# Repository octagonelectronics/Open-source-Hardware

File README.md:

# Open-source-Hardware
This repository contains all the Open-source hardware that we design.

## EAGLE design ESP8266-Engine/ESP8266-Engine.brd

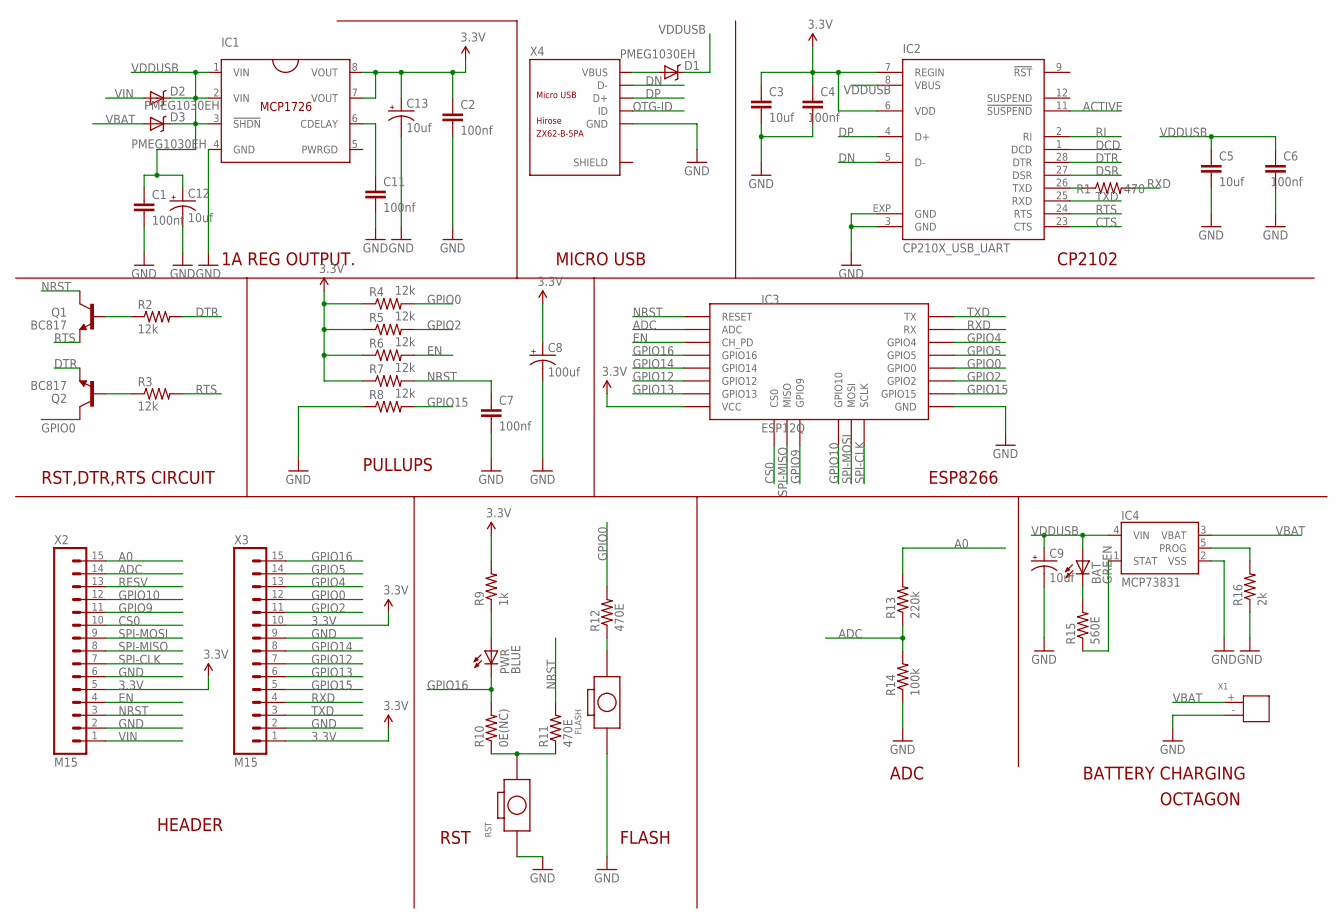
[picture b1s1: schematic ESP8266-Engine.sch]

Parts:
BAT: GREEN; LED-0603
C1, C2, C4, C6, C7, C11: 100nf; C0402
C3, C5: 10uf; C0603
C8: 100uf; EIA3216
C9, C12, C13: 10uf; EIA3216
D1, D2, D3: PMEG1030EH; MINIMELF
FLASH: SMD-BUTTON-WITHOUT-BOSS-(2P-3X2.5MM); SW2-SMD-3.0X2.5X1.2+0.4MM
IC1: MCP1726; SOIC8
IC2: CP210X_USB_UART; MLP28
IC3: ESP12Q
IC4: MCP73831; SOT23-5
PWR: BLUE; LED-0603
Q1, Q2: BC817; SOT23
R1: 470; R0402
R2, R3, R4, R5, R6, R7, R8: 12k; R0402
R9: 1k; R0402
R10: 0E(NC); R0402
R11, R12: 470E; R0402
R13: 220k; R0402
R14: 100k; R0402
R15: 560E; R0402
R16: 2k; R0402
RST: SMD-BUTTON-WITHOUT-BOSS-(2P-3X2.5MM); SW2-SMD-3.0X2.5X1.2+0.4MM
X1: DIP-JST-2P-2.0; H2-2.0-6X4.5MM
X2, X3: M15; 1X15
X4: MICRO-USB-SMD(ZX62-B-5PA); MICRO-USB5+6P-SMD-0.65-AB

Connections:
3.3V: C2.1, C3.1, C4.1, C8.A (+), C13.A (+), IC1.7 (VOUT), IC1.8 (VOUT), IC2.6 (VDD), IC2.7 (REGIN), IC3.VCC, R4.1, R5.1, R6.1, R7.1, R9.2, X2.5, X3.1, X3.10
A0: R13.2, X2.15
ACTIVE: IC2.11 (!SUSPEND)
ADC: IC3.ADC, R13.1, R14.2, X2.14
CS0: IC3.CS0, X2.10
CTS: IC2.23 (CTS)
DCD: IC2.1 (DCD)
DN: IC2.5 (D-), X4.2 (D-)
DP: IC2.4 (D+), X4.3 (D+)
DSR: IC2.27 (DSR)
DTR: IC2.28 (DTR), Q2.2 (E), R2.2
EN: IC3.EN (CH_PD), R6.2, X2.4
GND: C1.2, C2.2, C3.2, C4.2, C5.2, C6.2, C7.2, C8.C (-), C9.C (-), C11.2, C12.C (-), C13.C (-), FLASH.1, IC1.4 (GND), IC2.3 (GND), IC2.EXP (GND), IC3.GND, IC4.2 (VSS), R8.1, R14.1, R16.1, RST.1, X1.-, X2.2, X2.6, X3.2, X3.9, X4.5 (GND)
GPIO0: IC3.GPIO0, Q2.3 (C), R4.2, R12.2, X3.12
GPIO2: IC3.GPIO2, R5.2, X3.11
GPIO4: IC3.GPIO4, X3.13
GPIO5: IC3.GPIO5, X3.14
GPIO9: IC3.GPIO9, X2.11
GPIO10: IC3.GPIO10, X2.12
GPIO12: IC3.GPIO12, X3.7
GPIO13: IC3.GPIO13, X3.6
GPIO14: IC3.GPIO14, X3.8
GPIO15: IC3.GPIO15, R8.2, X3.5
GPIO16: IC3.GPIO16, PWR.C, R10.2, X3.15
unnamed: Q1.1 (B), R2.1
unnamed: IC2.26 (TXD), R1.1
unnamed: Q2.1 (B), R3.1
unnamed: BAT.C, R15.2
unnamed: IC4.1 (STAT), R15.1
unnamed: FLASH.2, R12.1
unnamed: PWR.A, R9.1
unnamed: R10.1, R11.1, RST.2
unnamed: IC4.5 (PROG), R16.2
unnamed: C11.1, IC1.6 (CDELAY)
NRST: C7.1, IC3.RESET, Q1.3 (C), R7.2, R11.2, X2.3
OTG-ID: X4.4 (ID)
RESV: X2.13
RI: IC2.2 (RI)
RTS: IC2.24 (RTS), Q1.2 (E), R3.2
RXD: IC3.RX, R1.2, X3.4
SPI-CLK: IC3.SCLK, X2.7
SPI-MISO: IC3.MISO, X2.8
SPI-MOSI: IC3.MOSI, X2.9
TXD: IC2.25 (RXD), IC3.TX, X3.3
VBAT: D3.A, IC4.3 (VBAT), X1.+
VBUS: D1.A, X4.1 (VBUS)
VDDUSB: BAT.A, C1.1, C5.1, C6.1, C9.A (+), C12.A (+), D1.K (C), D2.K (C), D3.K (C), IC1.1 (VIN), IC1.2 (VIN), IC1.3 (!SHDN), IC2.8 (VBUS), IC4.4 (VIN)
VIN: D2.A, X2.1

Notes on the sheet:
OCTAGON
1A REG OUTPUT.
MICRO USB
CP2102
RST,DTR,RTS CIRCUIT
PULLUPS
ESP8266
HEADER
RST
FLASH
ADC
BATTERY CHARGING

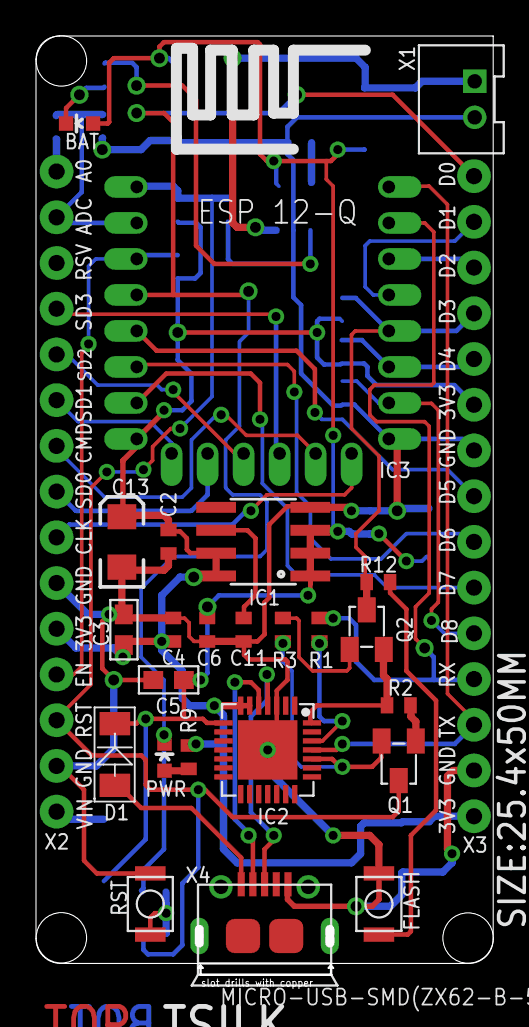
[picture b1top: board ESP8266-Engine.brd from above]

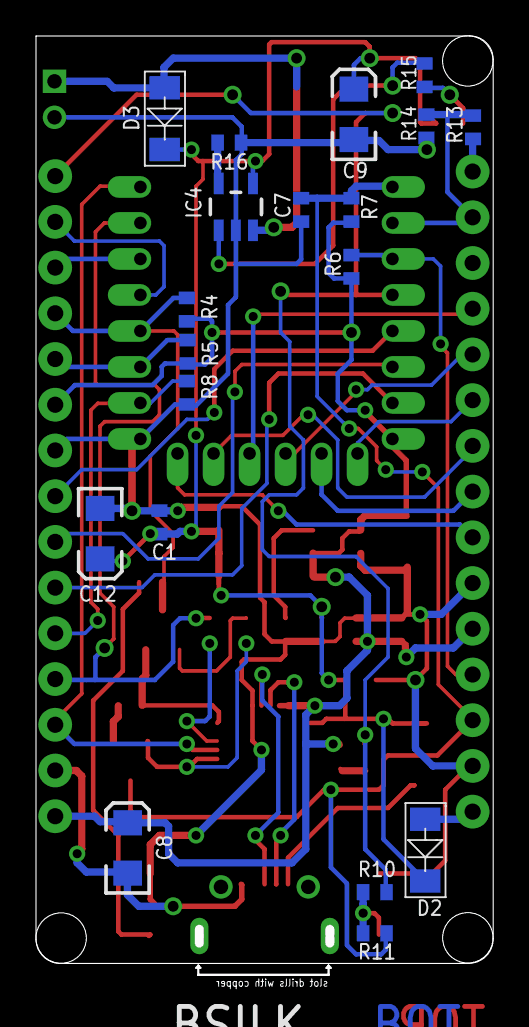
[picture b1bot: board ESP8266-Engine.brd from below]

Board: 2 copper layers, 24.9 x 52.5 mm, 45 parts (19 on the bottom side), 41 nets.

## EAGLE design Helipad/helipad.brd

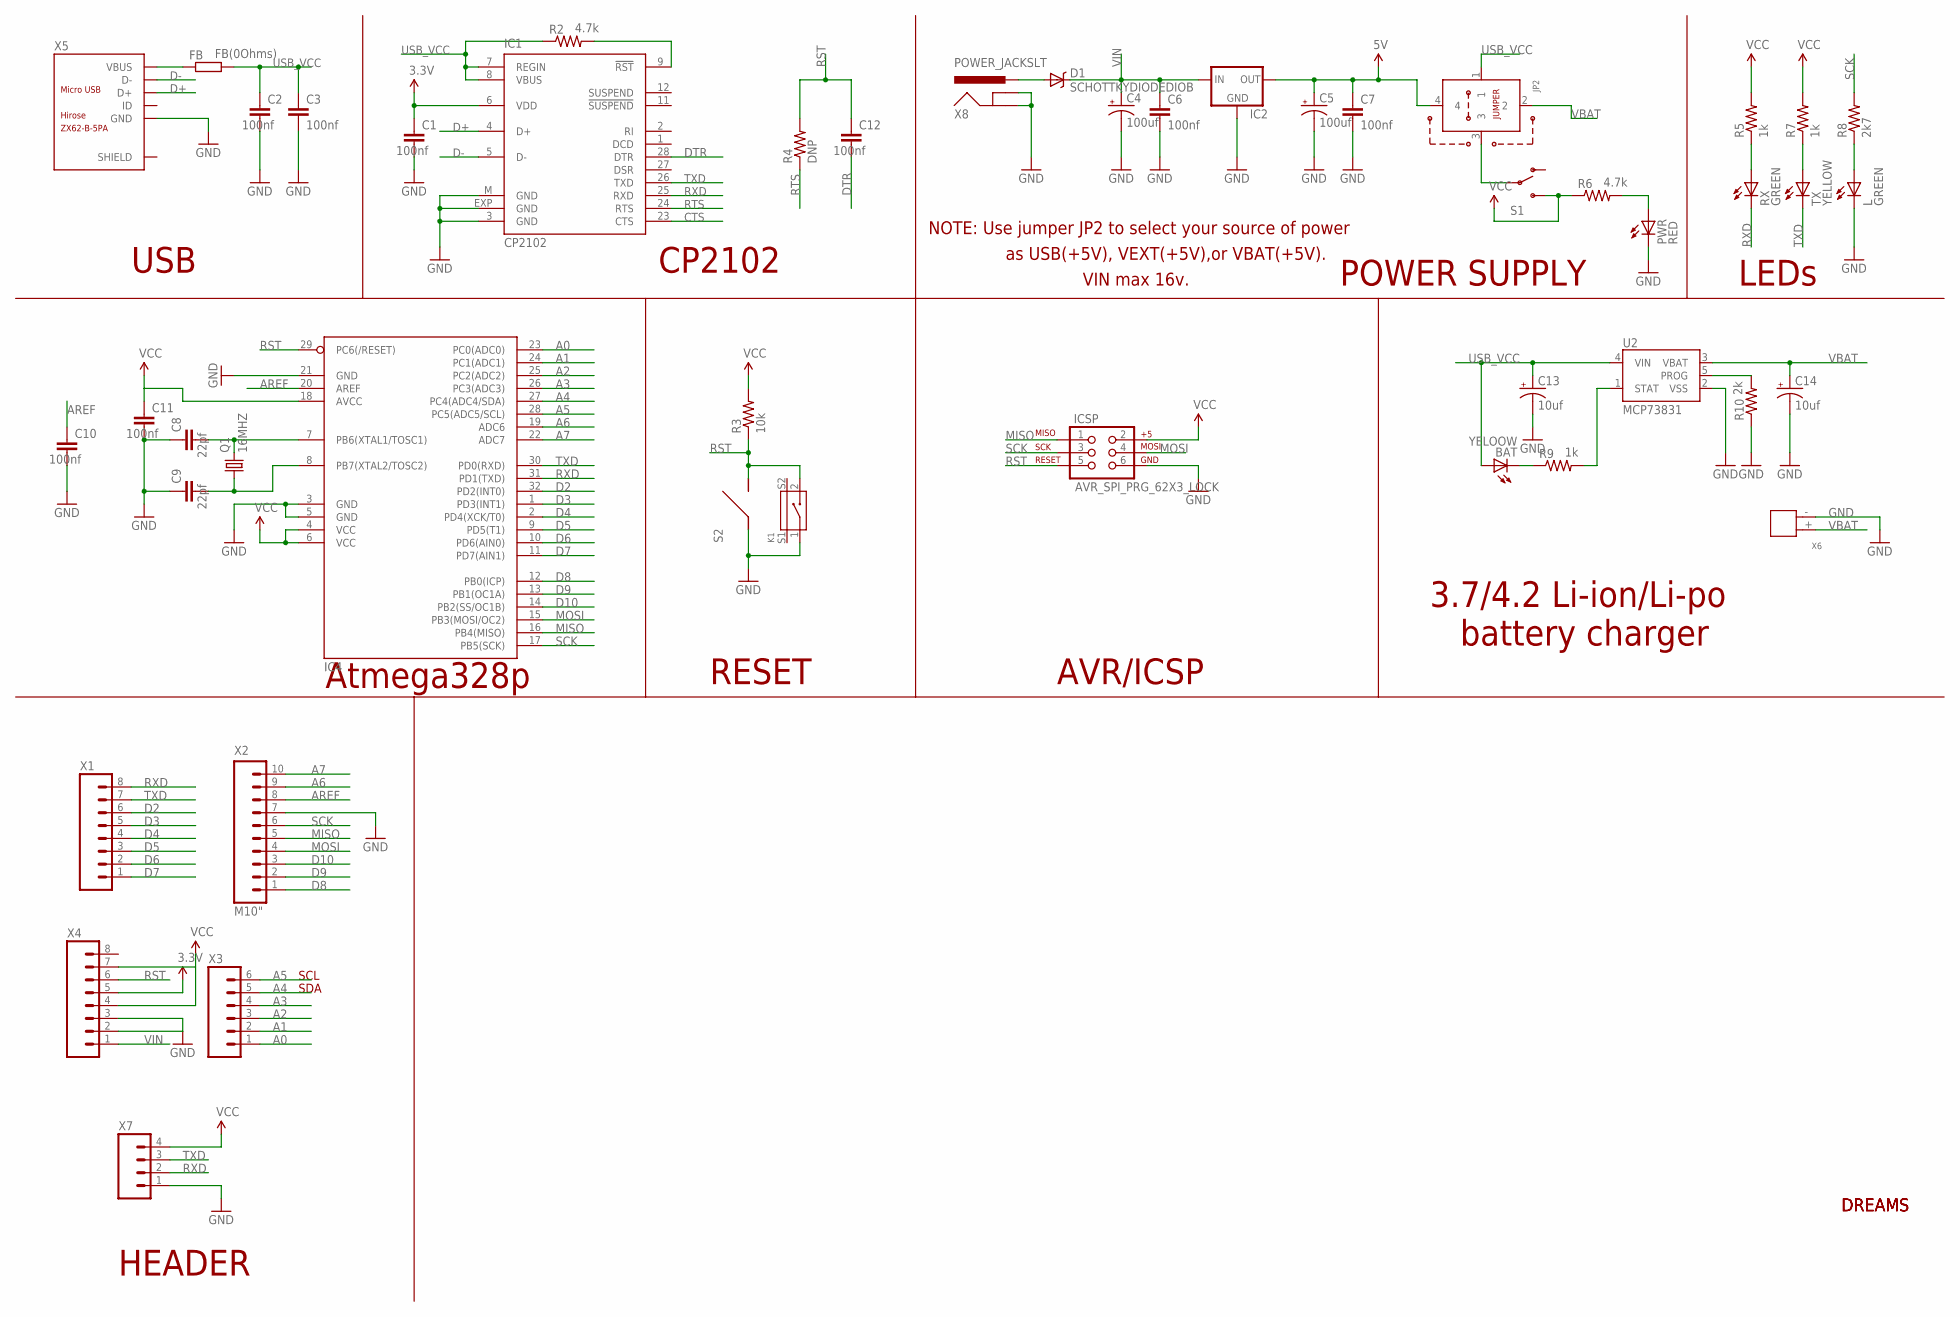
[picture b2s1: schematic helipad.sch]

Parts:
BAT: YELOOW; LED-1206
C1, C2, C3, C6, C7, C10, C11, C12: 100nf; C0603
C4, C5: 100uf; EIA7343
C8, C9: 22pf; C0603
C13, C14: 10uf; EIA3216
D1: SCHOTTKYDIODEDIOB; MINIMELF
FB: FB(0Ohms); R0603
IC1: CP2102; MLP28
IC2: V_REG_78XXX; DPAK
IC4: MEGA8-TQFP32-AI; TQFP32-08
ICSP: AVR_SPI_PRG_62X3_LOCK; 2X3_LOCK
JP2: JUMPER_3WAY
K1: SMD-BUTTON-2+2P; SW4-SMD-7.0X3.5X3.5MM-90D
L: GREEN; LED-1206
PWR: RED; LED-1206
Q1: 16MHZ; HC49U-V
R2, R6: 4.7k; R0603
R3: 10k; R0603
R4: DNP; R0603
R5, R7, R9: 1k; R0603
R8: 2k7; R0603
R10: 2k; R0603
RX: GREEN; LED-1206
S1: SWITCH-SPSTSMD2; SWITCH-SPDT-SMD
S2: TACT_SWITCH_SIDE; TACT-SWITCH_SIDE
TX: YELLOW; LED-1206
U2: MCP73831; SOT23-5
X1, X4: M08; 1X08
X2: M10"; 1X10
X3: M06SIP; 1X06
X5: MICRO-USB-SMD(ZX62-B-5PA); MICRO-USB5+6P-SMD-0.65-AB
X6: DIP-JST-2P-2.0; H2-2.0-6X4.5MM
X7: M04PTH; 1X04
X8: POWER_JACKSLT; POWER_JACK_SLOT

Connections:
3.3V: C1.1, IC1.6 (VDD), X4.5
5V: C5.A (+), C7.1, IC2.3 (OUT), JP2.4
A0: IC4.23 (PC0(ADC0)), X3.1
A1: IC4.24 (PC1(ADC1)), X3.2
A2: IC4.25 (PC2(ADC2)), X3.3
A3: IC4.26 (PC3(ADC3)), X3.4
A4: IC4.27 (PC4(ADC4/SDA)), X3.5
A5: IC4.28 (PC5(ADC5/SCL)), X3.6
A6: IC4.19 (ADC6), X2.9
A7: IC4.22 (ADC7), X2.10
AREF: C10.1, X2.8
CTS: IC1.23 (CTS)
D2: IC4.32 (PD2(INT0)), X1.6
D3: IC4.1 (PD3(INT1)), X1.5
D4: IC4.2 (PD4(XCK/T0)), X1.4
D5: IC4.9 (PD5(T1)), X1.3
D6: IC4.10 (PD6(AIN0)), X1.2
D7: IC4.11 (PD7(AIN1)), X1.1
D8: IC4.12 (PB0(ICP)), X2.1
D9: IC4.13 (PB1(OC1A)), X2.2
D10: IC4.14 (PB2(SS/OC1B)), X2.3
D+: IC1.4 (D+), X5.3 (D+)
D-: IC1.5 (D-), X5.2 (D-)
DTR: C12.2, IC1.28 (DTR)
GND: C1.2, C2.2, C3.2, C4.C (-), C5.C (-), C6.2, C7.2, C8.1, C9.1, C10.2, C11.2, C13.C (-), C14.C (-), IC1.3 (GND), IC1.EXP (GND), IC1.M (GND), IC2.2 (GND), IC4.3 (GND), IC4.5 (GND), IC4.21 (GND), ICSP.6, K1.1, L.C, PWR.C, R10.1, S2.P$1 (1), U2.2 (VSS), X2.7, X4.2, X4.3, X5.5 (GND), X6.-, X7.1, X8.GND@1 (GNDBREAK), X8.GND@2 (GND)
MISO: IC4.16 (PB4(MISO)), ICSP.1, X2.5
MOSI: IC4.15 (PB3(MOSI/OC2)), ICSP.4, X2.4
unnamed: D1.A, X8.PWR
unnamed: IC1.9 (!RST), R2.2
unnamed: PWR.A, R6.2
unnamed: JP2.3, S1.2
unnamed: R5.1, RX.A
unnamed: C8.2, IC4.7 (PB6(XTAL1/TOSC1)), Q1.2
unnamed: C9.2, IC4.8 (PB7(XTAL2/TOSC2)), Q1.1
unnamed: R7.1, TX.A
unnamed: L.A, R8.1
unnamed: BAT.C, R9.1
unnamed: R9.2, U2.1 (STAT)
unnamed: R10.2, U2.5 (PROG)
RST: C12.1, IC4.29 (PC6(/RESET)), ICSP.5, K1.2, R3.1, R4.2, S2.P$2 (2), X4.6
RTS: IC1.24 (RTS), R4.1
RXD: IC1.25 (RXD), IC4.31 (PD1(TXD)), RX.C, X1.8, X7.2
SCK: IC4.17 (PB5(SCK)), ICSP.3, R8.2, X2.6
TXD: IC1.26 (TXD), IC4.30 (PD0(RXD)), TX.C, X1.7, X7.3
USB_VCC: BAT.A, C2.1, C3.1, C13.A (+), FB.2, IC1.7 (REGIN), IC1.8 (VBUS), JP2.1, R2.1, U2.4 (VIN)
VBAT: C14.A (+), JP2.2, U2.3 (VBAT), X6.+
VBUS: FB.1, X5.1 (VBUS)
VCC: C11.1, IC4.4 (VCC), IC4.6 (VCC), IC4.18 (AVCC), ICSP.2, R3.2, R5.2, R6.1, R7.2, S1.3 (S), X4.4, X4.7, X7.4
VIN: C4.A (+), C6.1, D1.K (C), IC2.1 (IN), X4.1

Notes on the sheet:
DREAMS
SDA
SCL
NOTE: Use jumper JP2 to select your source of power
as USB(+5V), VEXT(+5V),or VBAT(+5V).
VIN max 16v.
USB
CP2102
POWER SUPPLY
LEDs
Atmega328p
RESET
AVR/ICSP
3.7/4.2 Li-ion/Li-po battery charger
HEADER

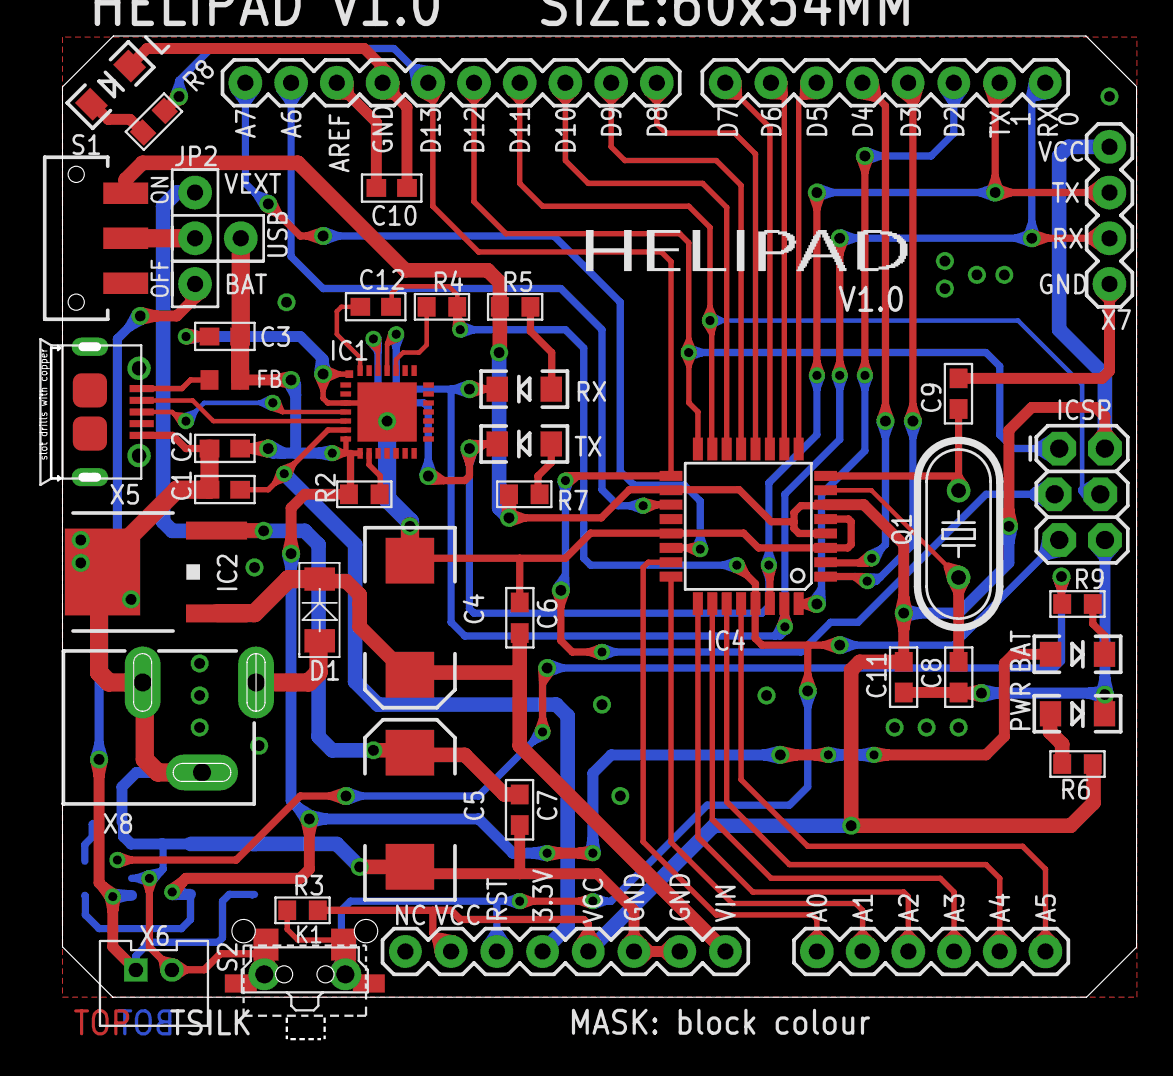
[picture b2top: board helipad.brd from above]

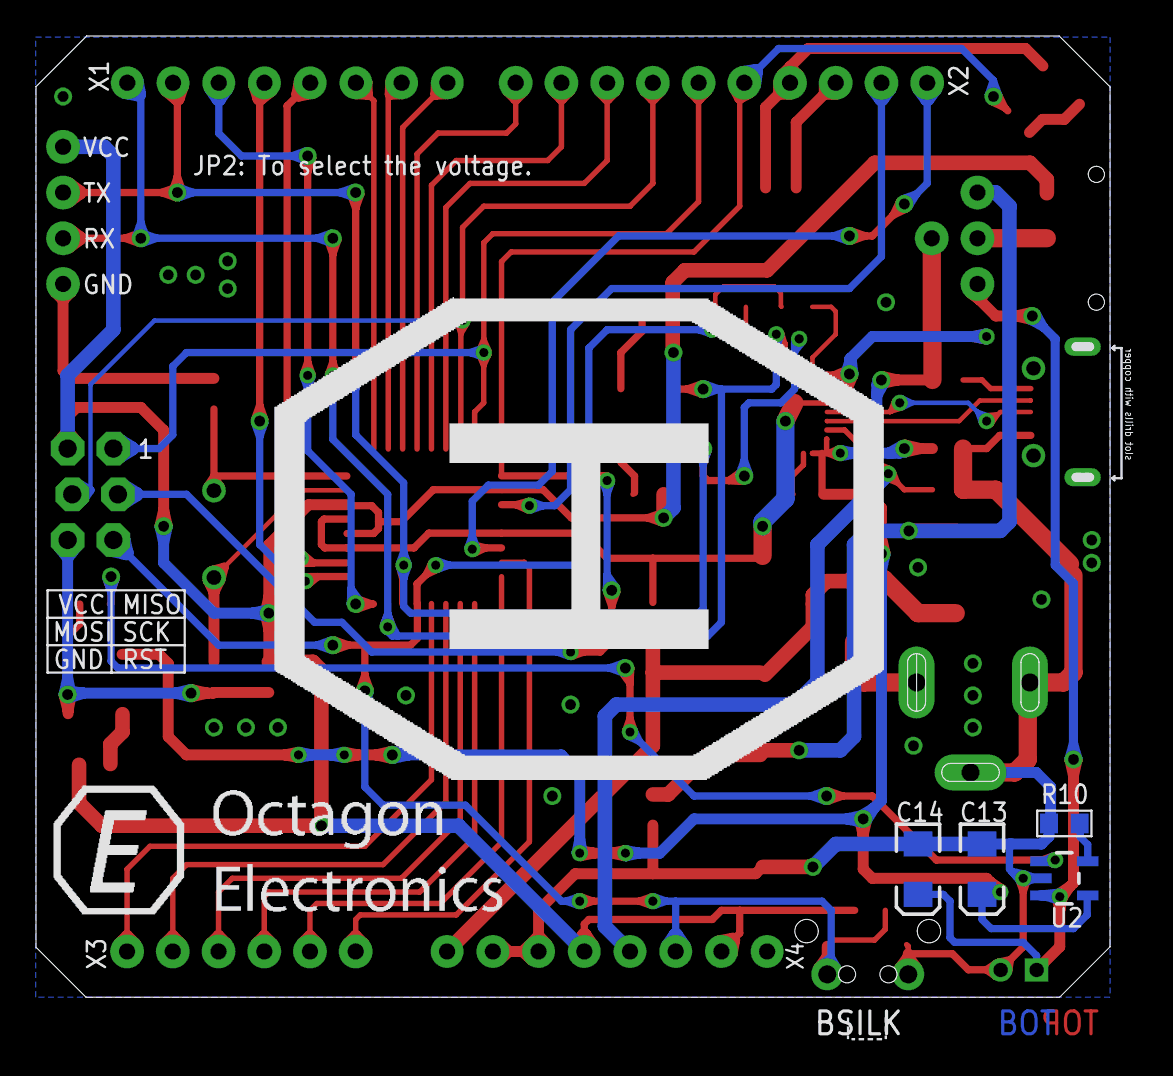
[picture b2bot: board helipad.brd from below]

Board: 2 copper layers, 60.6 x 55.3 mm, 48 parts (4 on the bottom side), 48 nets.

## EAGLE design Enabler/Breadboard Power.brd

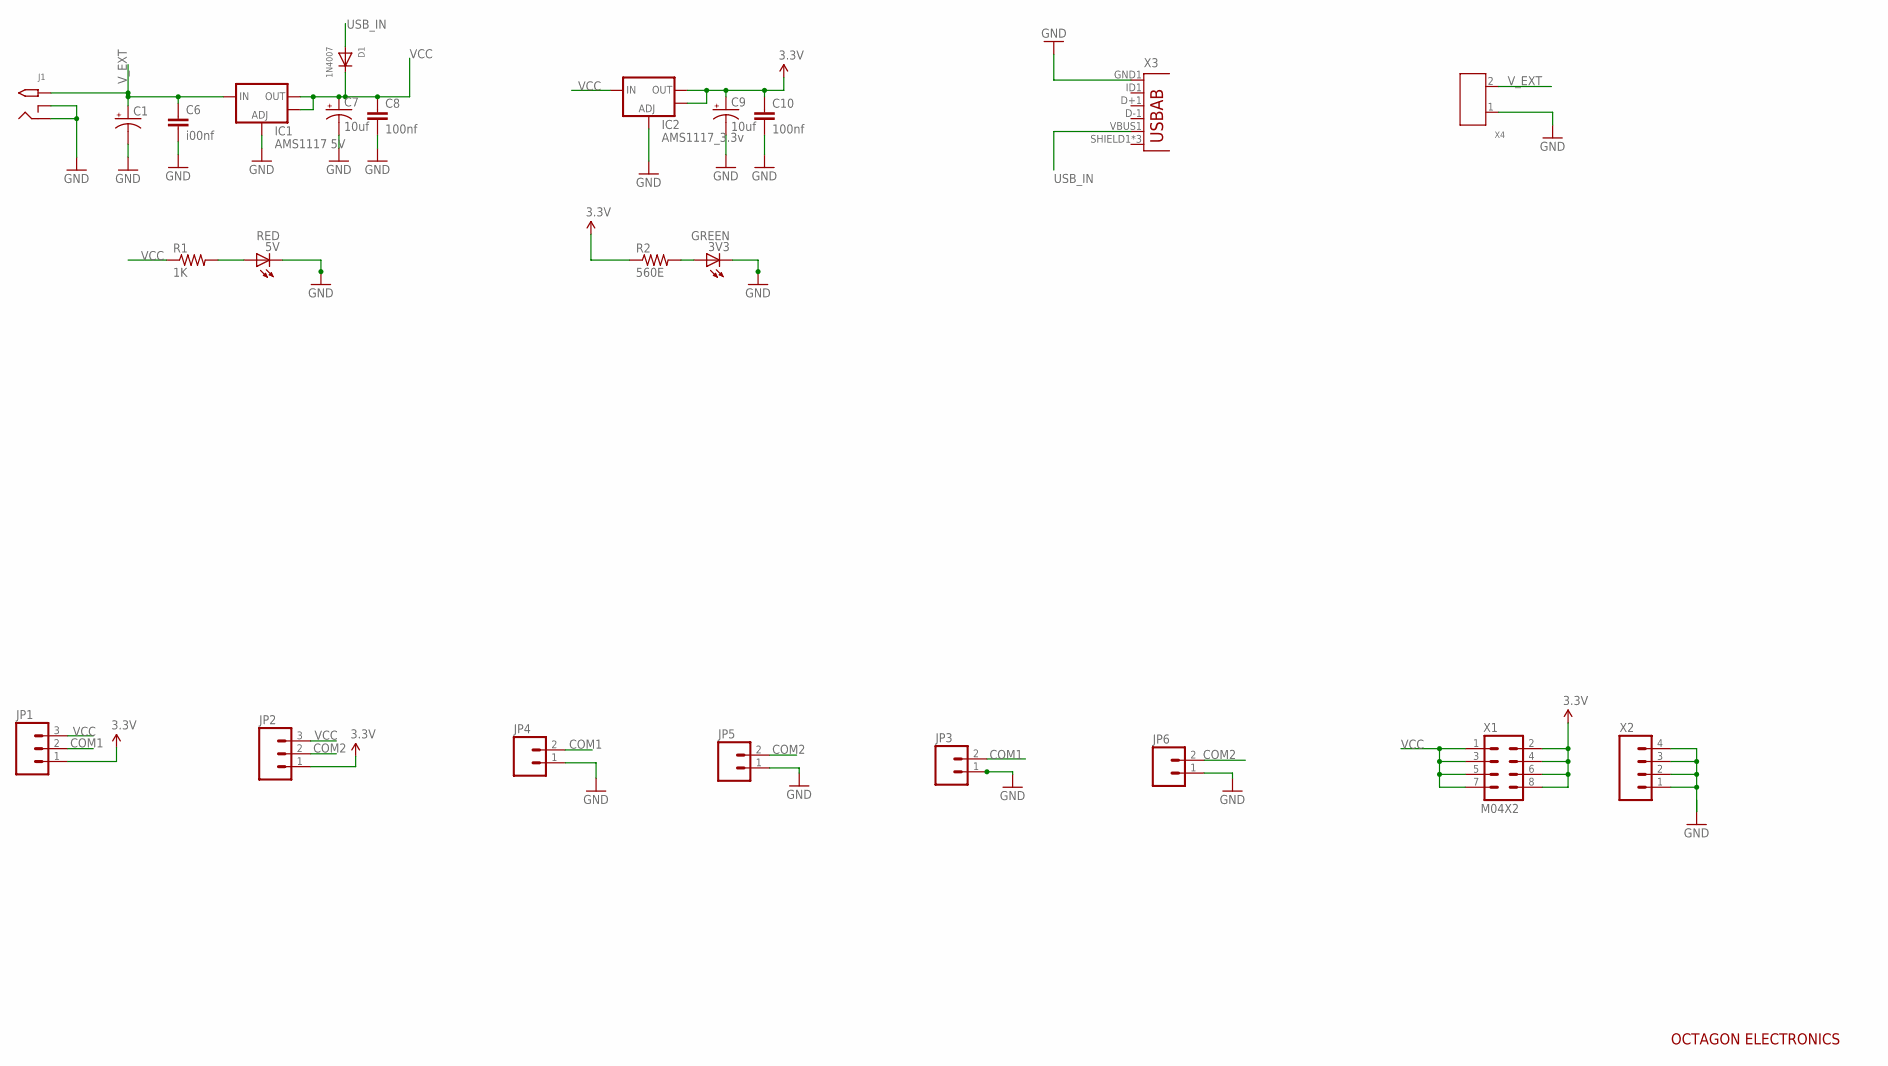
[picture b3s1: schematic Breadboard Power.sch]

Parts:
3V3: GREEN; LED-0603
5V: RED; LED-0603
C1: CAPACITOR_POLARIZEDC; PANASONIC_C
C6: i00nf; C0603
C7, C9: 10uf; EIA3216
C8, C10: 100nf; C0603
D1: 1N4007; SMADIODE
IC1: AMS1117 5V; SOT223
IC2: AMS1117_3.3v; SOT223
J1: 2.1MMJACKTHM; PJ-102A
JP1, JP2: M03PTH; 1X03
JP3, JP4, JP5, JP6: M02PTH; 1X02
R1: 1K; R0603
R2: 560E; R0603
X1: M04X2; 2X4
X2: M04PTH; 1X04
X3: USB-ABCONN-11794; USB-AB-MICRO-SMD_V03
X4: SCREW-TERMINAL-GREEN(2P-5.0); H2-5.0-10.5X8.0MM

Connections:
3.3V: C9.A (+), C10.1, IC2.2 (OUT), IC2.4 (OUT), JP1.1, JP2.1, R2.1, X1.2, X1.4, X1.6, X1.8
COM1: JP1.2, JP3.2, JP4.2
COM2: JP2.2, JP5.2, JP6.2
GND: 3V3.C, 5V.C, C1.-, C6.2, C7.C (-), C8.2, C9.C (-), C10.2, IC1.1 (ADJ), IC2.1 (ADJ), J1.RING, J1.RING_SW, JP3.1, JP4.1, JP5.1, JP6.1, X2.1, X2.2, X2.3, X2.4, X3.GND1 (GND), X4.1
unnamed: 5V.A, R1.2
unnamed: 3V3.A, R2.2
USB_IN: D1.A, X3.VBUS1 (VBUS)
VCC: C7.A (+), C8.1, D1.C, IC1.2 (OUT), IC1.4 (OUT), IC2.3 (IN), JP1.3, JP2.3, R1.1, X1.1, X1.3, X1.5, X1.7
V_EXT: C1.+, C6.1, IC1.3 (IN), J1.TIP, X4.2

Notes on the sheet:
OCTAGON ELECTRONICS

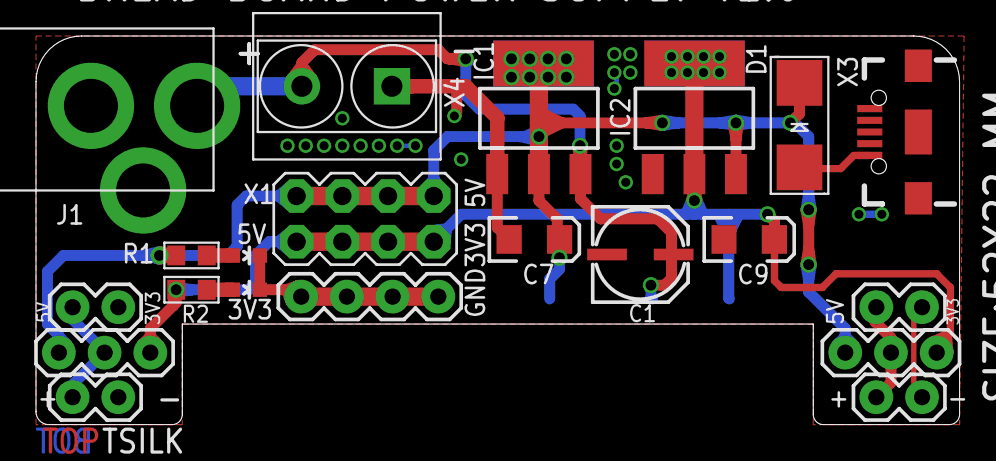
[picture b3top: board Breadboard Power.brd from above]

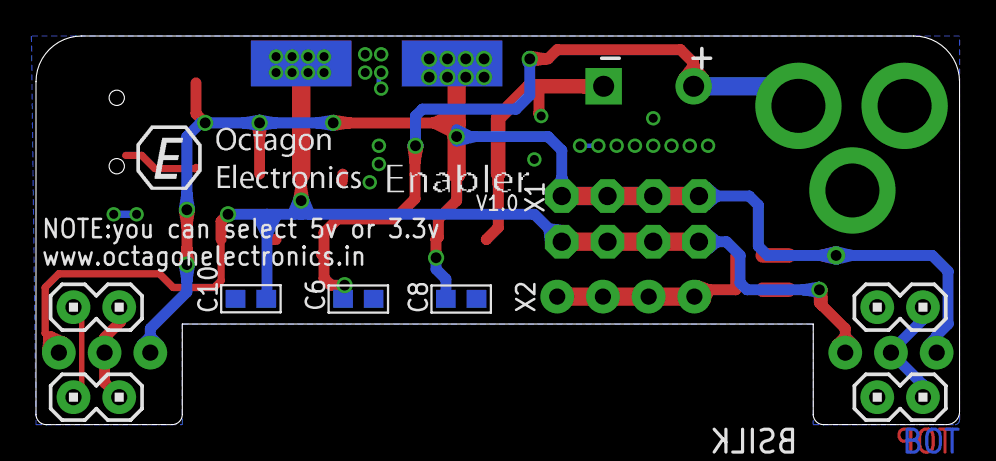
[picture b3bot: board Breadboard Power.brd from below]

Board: 2 copper layers, 51.3 x 21.6 mm, 24 parts (3 on the bottom side), 9 nets.

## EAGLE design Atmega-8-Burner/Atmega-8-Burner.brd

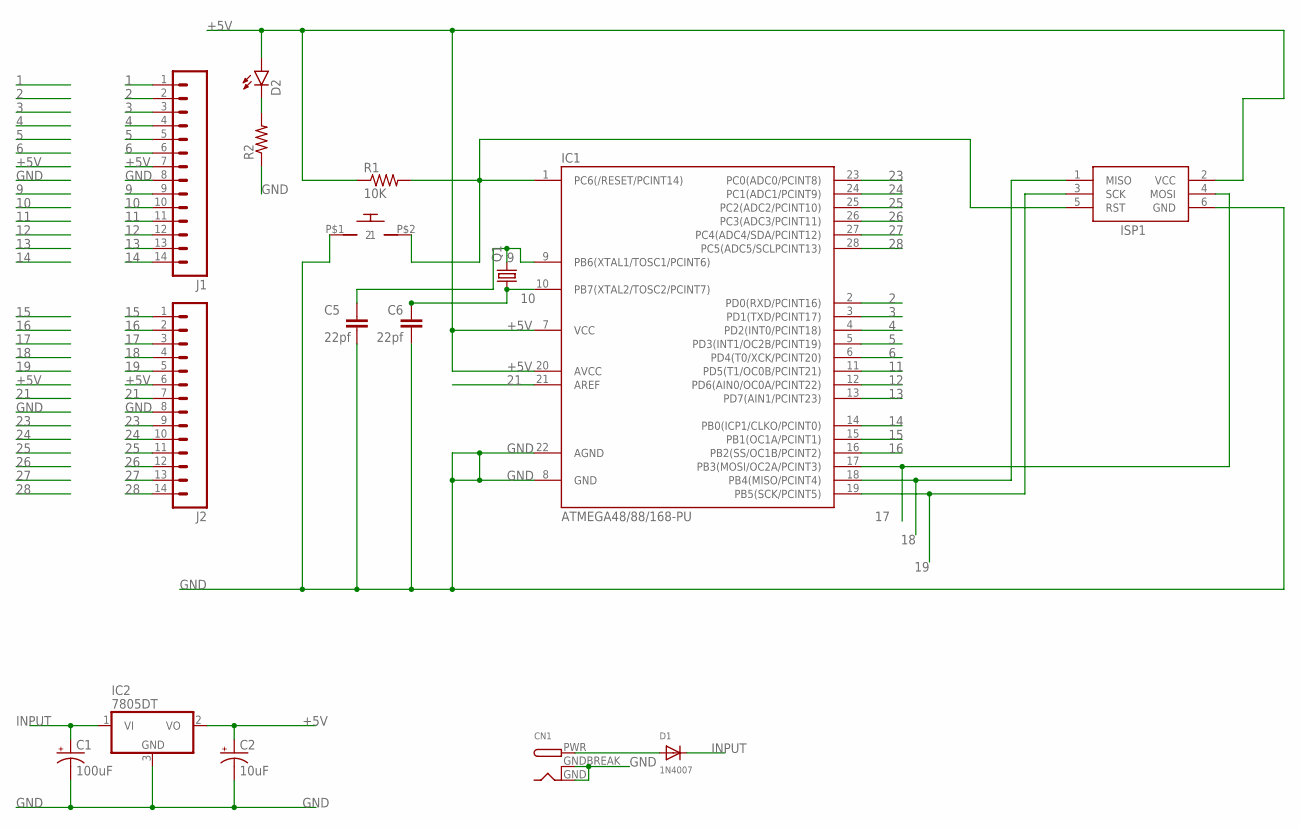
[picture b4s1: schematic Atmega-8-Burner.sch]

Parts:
C1: 100uF; PANASONIC_C
C2: 10uF; PANASONIC_C
C5, C6: 22pf; 0603-CAP
CN1: DCBARRELPTH; DCJACK_2MM_PTH
D1: 1N4007; SMADIODE
D2: LED0603; LED-0603
IC1: ATMEGA48/88/168-PU; DIL28-3
IC2: 7805DT; TO252
ISP1: AVRISP-6; AVRISP
J1, J2: M14LOCK; 1X14_LOCK
Q1: CRYSTALHC49U-V; HC49U-V
R1: 10K; R0603
R2: RESISTOR0603-RES; 0603-RES
U$1: TAC_SWITCH

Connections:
1: IC1.1 (PC6(/RESET/PCINT14)), ISP1.5 (RST), J1.1, R1.2, U$1.P$2 (2)
2: IC1.2 (PD0(RXD/PCINT16)), J1.2
3: IC1.3 (PD1(TXD/PCINT17)), J1.3
4: IC1.4 (PD2(INT0/PCINT18)), J1.4
5: IC1.5 (PD3(INT1/OC2B/PCINT19)), J1.5
6: IC1.6 (PD4(T0/XCK/PCINT20)), J1.6
9: C5.1, IC1.9 (PB6(XTAL1/TOSC1/PCINT6)), J1.9, Q1.2
10: C6.1, IC1.10 (PB7(XTAL2/TOSC2/PCINT7)), J1.10, Q1.1
11: IC1.11 (PD5(T1/OC0B/PCINT21)), J1.11
12: IC1.12 (PD6(AIN0/OC0A/PCINT22)), J1.12
13: IC1.13 (PD7(AIN1/PCINT23)), J1.13
14: IC1.14 (PB0(ICP1/CLKO/PCINT0)), J1.14
15: IC1.15 (PB1(OC1A/PCINT1)), J2.1
16: IC1.16 (PB2(SS/OC1B/PCINT2)), J2.2
17: IC1.17 (PB3(MOSI/OC2A/PCINT3)), ISP1.4 (MOSI), J2.3
18: IC1.18 (PB4(MISO/PCINT4)), ISP1.1 (MISO), J2.4
19: IC1.19 (PB5(SCK/PCINT5)), ISP1.3 (SCK), J2.5
21: IC1.21 (AREF), J2.7
23: IC1.23 (PC0(ADC0/PCINT8)), J2.9
24: IC1.24 (PC1(ADC1/PCINT9)), J2.10
25: IC1.25 (PC2(ADC2/PCINT10)), J2.11
26: IC1.26 (PC3(ADC3/PCINT11)), J2.12
27: IC1.27 (PC4(ADC4/SDA/PCINT12)), J2.13
28: IC1.28 (PC5(ADC5/SCLPCINT13)), J2.14
+5V: C2.+, D2.A, IC1.7 (VCC), IC1.20 (AVCC), IC2.2 (VO), ISP1.2 (VCC), J1.7, J2.6, R1.1
GND: C1.-, C2.-, C5.2, C6.2, CN1.GND, CN1.GNDBREAK, IC1.8 (GND), IC1.22 (AGND), IC2.3 (GND), ISP1.6 (GND), J1.8, J2.8, R2.1, U$1.P$1 (1)
INPUT: C1.+, D1.C, IC2.1 (VI)
unnamed: CN1.PWR, D1.A
unnamed: D2.C, R2.2

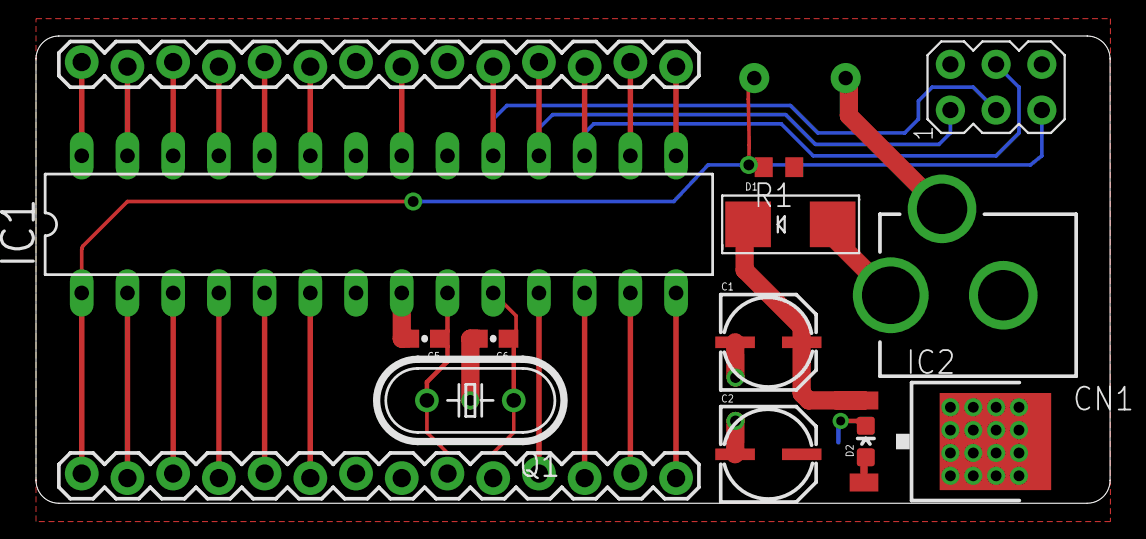
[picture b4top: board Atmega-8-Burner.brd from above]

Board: 2 copper layers, 59.7 x 26.0 mm, 16 parts (1 on the bottom side), 29 nets.

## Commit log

2017-10-27 Added board, schematic and specification files.
2017-10-27 Added board and schematic files.

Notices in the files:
parts and their libraries:
SparkFun-Capacitors: Licensing: Creative Commons ShareAlike 4.0 International - https://creativecommons.org/licenses/by-sa/4.0
